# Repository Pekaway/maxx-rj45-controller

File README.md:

# maxx-rj45-controller
i2c expansion board to control the MaxxFan via rj45 port. 
Its based on the work from Zef Houssney.
https://zef.studio/projects/maxxfan/

The circuit board is in production and will be **tested soon**. It will then be integrated into the **VAN PI OS.** 
https://github.com/Pekaway/VAN_PI

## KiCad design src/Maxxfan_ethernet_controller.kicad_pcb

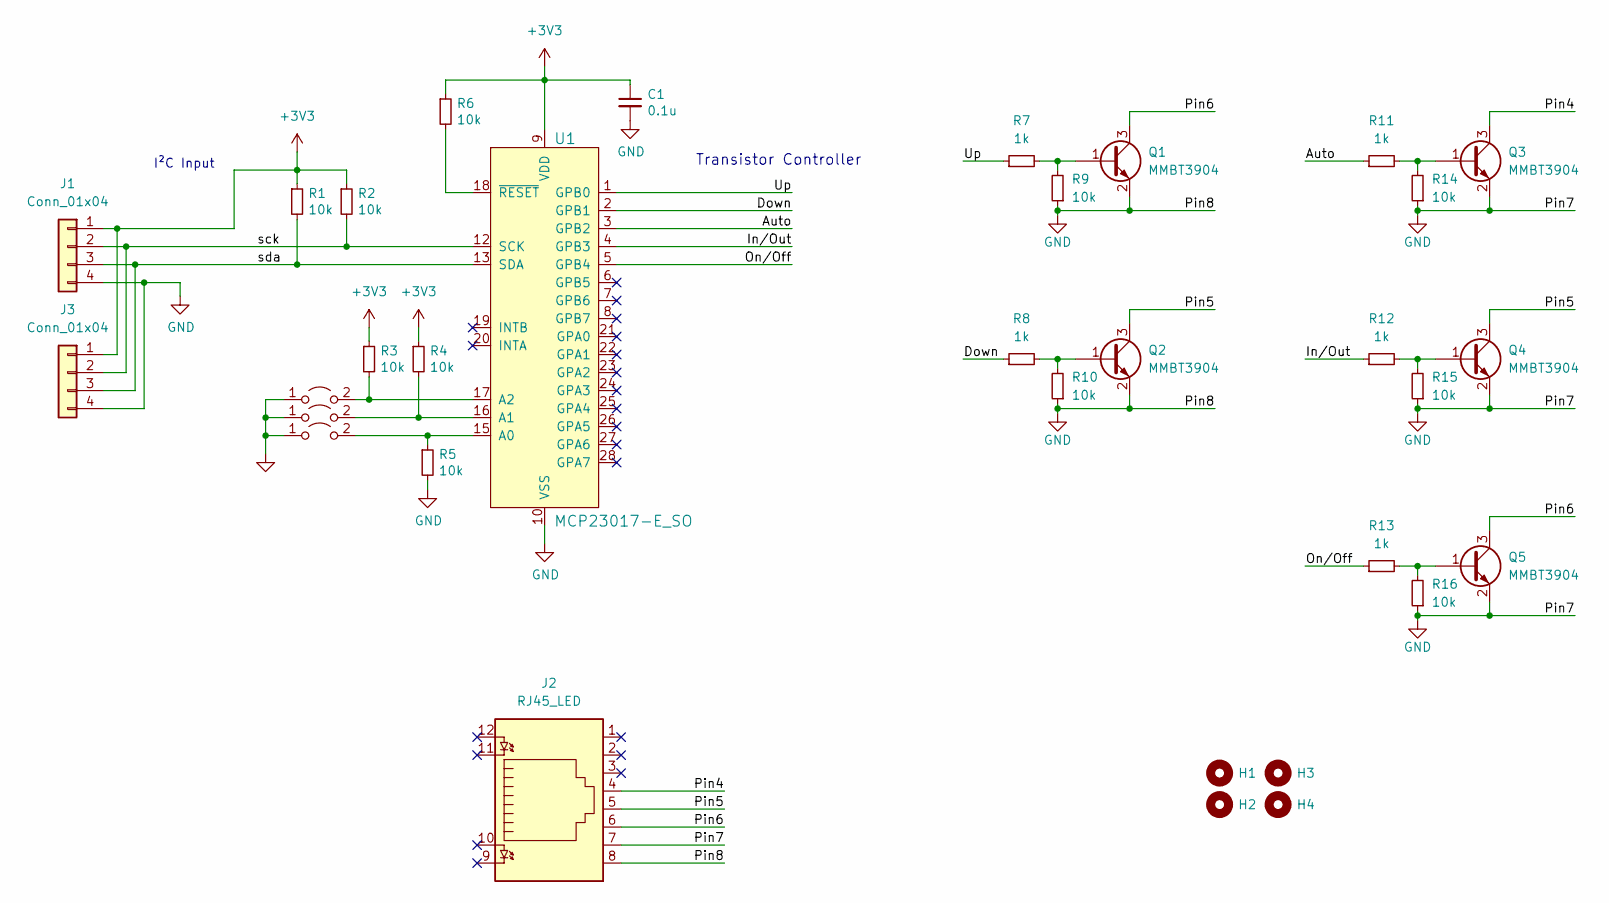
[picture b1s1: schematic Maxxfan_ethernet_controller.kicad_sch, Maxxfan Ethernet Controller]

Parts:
C1: 0.1u; C_0603_1608Metric
H1, H2, H3, H4: MountingHole; MountingHole_3.2mm_M3
J1, J3: Conn_01x04; JST_PH_S4B-PH-K_1x04_P2.00mm_Horizontal
J2: RJ45_LED; RJ45B*1*1
JP1, JP2, JP3: Jumper_2_Open; SolderJumper-2_P1.3mm_Open_RoundedPad1.0x1.5mm
Q1, Q2, Q3, Q4, Q5: MMBT3904; SOT-23
R1, R2, R3, R4, R5, R6, R9, R10, R14, R15, R16: 10k; R_0603_1608Metric
R7, R8, R11, R12, R13: 1k; R_0603_1608Metric
U1: MCP23017-E_SO; SOIC-28_W7.5mm; Mfr# MCP23017-E/SO-ND

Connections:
+3V3: C1.1, J1.1, J3.1, R1.1, R2.1, R3.1, R4.1, R6.1, U1.9 (VDD)
/Auto: R11.1, U1.3 (GPB2)
/Down: R8.1, U1.2 (GPB1)
/In/Out: R12.1, U1.4 (GPB3)
/On/Off: R13.1, U1.5 (GPB4)
/Pin4: J2.4, Q3.3 (C)
/Pin5: J2.5, Q2.3 (C), Q4.3 (C)
/Pin6: J2.6, Q1.3 (C), Q5.3 (C)
/Up: R7.1, U1.1 (GPB0)
/sck: J1.2, J3.2, R2.2, U1.12 (SCK)
/sda: J1.3, J3.3, R1.2, U1.13 (SDA)
unnamed: JP1.2 (B), R3.2, U1.17 (A2)
unnamed: JP2.2 (B), R4.2, U1.16 (A1)
unnamed: JP3.2 (B), R5.1, U1.15 (A0)
unnamed: Q1.1 (B), R7.2, R9.2
unnamed: Q2.1 (B), R8.2, R10.2
unnamed: Q3.1 (B), R11.2, R14.2
unnamed: Q4.1 (B), R12.2, R15.2
unnamed: Q5.1 (B), R13.2, R16.2
unnamed: R6.2, U1.18 (~RESET)

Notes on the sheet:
I²C Input
Transistor Controller

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
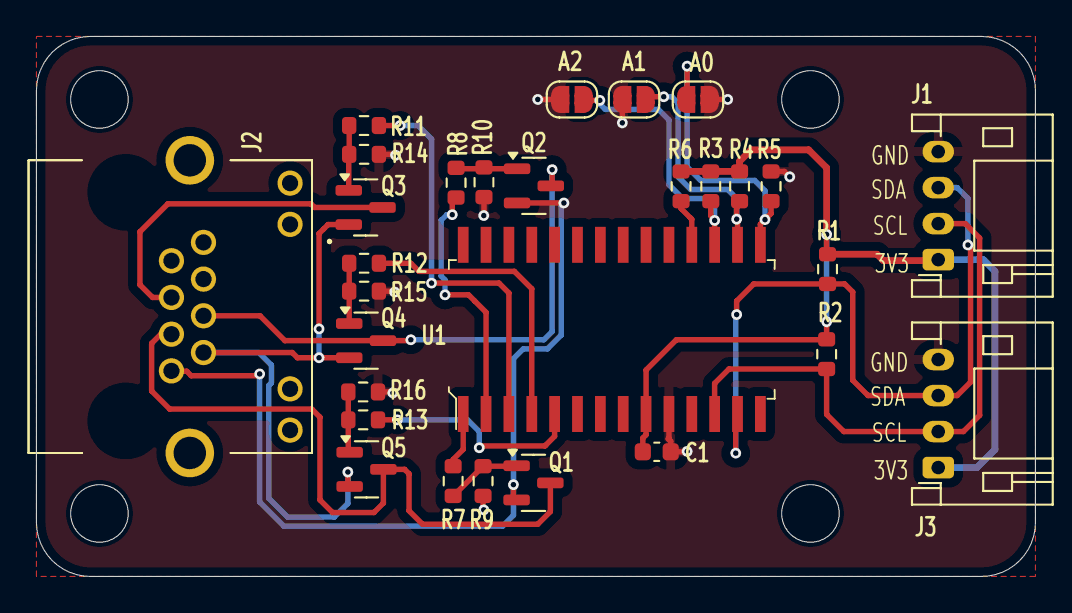
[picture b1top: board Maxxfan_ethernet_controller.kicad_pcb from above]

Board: 2 copper layers, 55.5 x 30.0 mm, 33 parts (0 on the bottom side), 23 nets.

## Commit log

2024-03-15 no message
